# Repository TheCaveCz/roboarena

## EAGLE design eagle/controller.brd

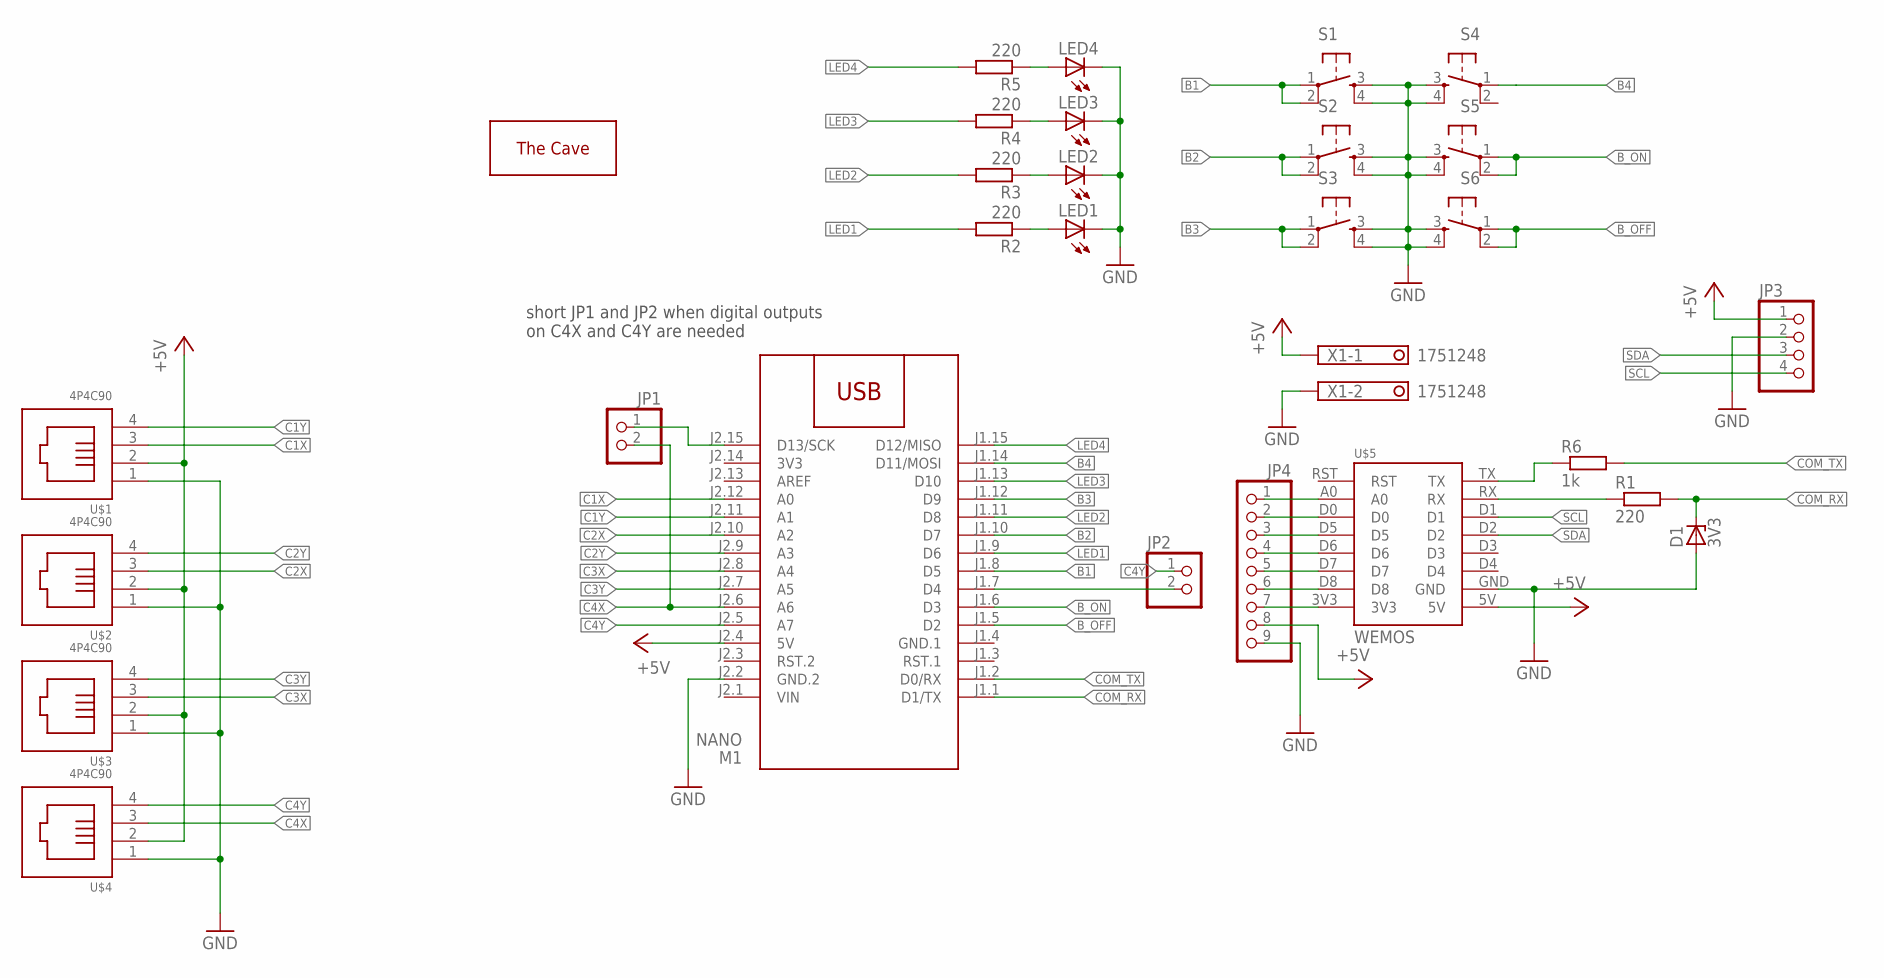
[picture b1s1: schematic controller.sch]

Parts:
D1: 3V3; ZDIO-7.5
JP1, JP2: PINHD-1X2; 1X02
JP3: PINHD-1X4; 1X04
JP4: PINHD-1X9; 1X09
LED1, LED2, LED3, LED4: LED5MM
M1: NANO; ARDUINO-NANO-3.0#NOHOLE
R1: 220; 0207/10
R2, R3, R4, R5: 220; R0805
R6: 1k; 0207/10
S1, S2, S3, S4, S5, S6: TACT-SWITCH-6MM-THT
U$1, U$2, U$3, U$4: 4P4C90; 4P4C-90
U$5: WEMOS
U$6: THECAVE_LOGO_NEW_TOP_SMALL; NEW_LOGO_SMALL_TOP
X1: 1751248

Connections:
3V3: M1.J2.14 (3V3)
+5V: JP3.1, JP4.8, M1.J2.4 (5V), U$1.2, U$2.2, U$3.2, U$4.2, U$5.5V, X1.1
B1: M1.J1.8 (D5), S1.1, S1.2
B2: M1.J1.10 (D7), S2.1, S2.2
B3: M1.J1.12 (D9), S3.1, S3.2
B4: M1.J1.14 (D11/MOSI), S4.1
B_OFF: M1.J1.5 (D2), S6.1, S6.2
B_ON: M1.J1.6 (D3), S5.1, S5.2
C1X: M1.J2.12 (A0), U$1.3
C1Y: M1.J2.11 (A1), U$1.4
C2X: M1.J2.10 (A2), U$2.3
C2Y: M1.J2.9 (A3), U$2.4
C3X: M1.J2.8 (A4), U$3.3
C3Y: M1.J2.7 (A5), U$3.4
C4X: JP1.2, M1.J2.6 (A6), U$4.3
C4Y: JP2.1, M1.J2.5 (A7), U$4.4
COM_RX: D1.C, M1.J1.1 (D1/TX), R1.2
COM_TX: M1.J1.2 (D0/RX), R6.2
GND: D1.A, JP3.2, JP4.9, LED1.K (C), LED2.K (C), LED3.K (C), LED4.K (C), M1.J2.2 (GND.2), S1.3, S1.4, S2.3, S2.4, S3.3, S3.4, S4.3, S4.4, S5.3, S5.4, S6.3, S6.4, U$1.1, U$2.1, U$3.1, U$4.1, U$5.GND, X1.2
GND.1: M1.J1.4 (GND.1)
LED1: M1.J1.9 (D6), R2.2
LED2: M1.J1.11 (D8), R3.2
LED3: M1.J1.13 (D10), R4.2
LED4: M1.J1.15 (D12/MISO), R5.2
unnamed: LED4.A, R5.1
unnamed: R1.1, U$5.RX
unnamed: LED3.A, R4.1
unnamed: LED2.A, R3.1
unnamed: LED1.A, R2.1
unnamed: JP1.1, M1.J2.15 (D13/SCK)
unnamed: JP2.2, M1.J1.7 (D4)
unnamed: JP4.2, U$5.D0
unnamed: JP4.3, U$5.D5
unnamed: JP4.4, U$5.D6
unnamed: JP4.5, U$5.D7
unnamed: JP4.6, U$5.D8
unnamed: JP4.1, U$5.A0
unnamed: R6.1, U$5.TX
unnamed: JP4.7, U$5.3V3
SCL: JP3.4, U$5.D1
SDA: JP3.3, U$5.D2
VIN: M1.J2.1 (VIN)

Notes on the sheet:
short JP1 and JP2 when digital outputs on C4X and C4Y are needed

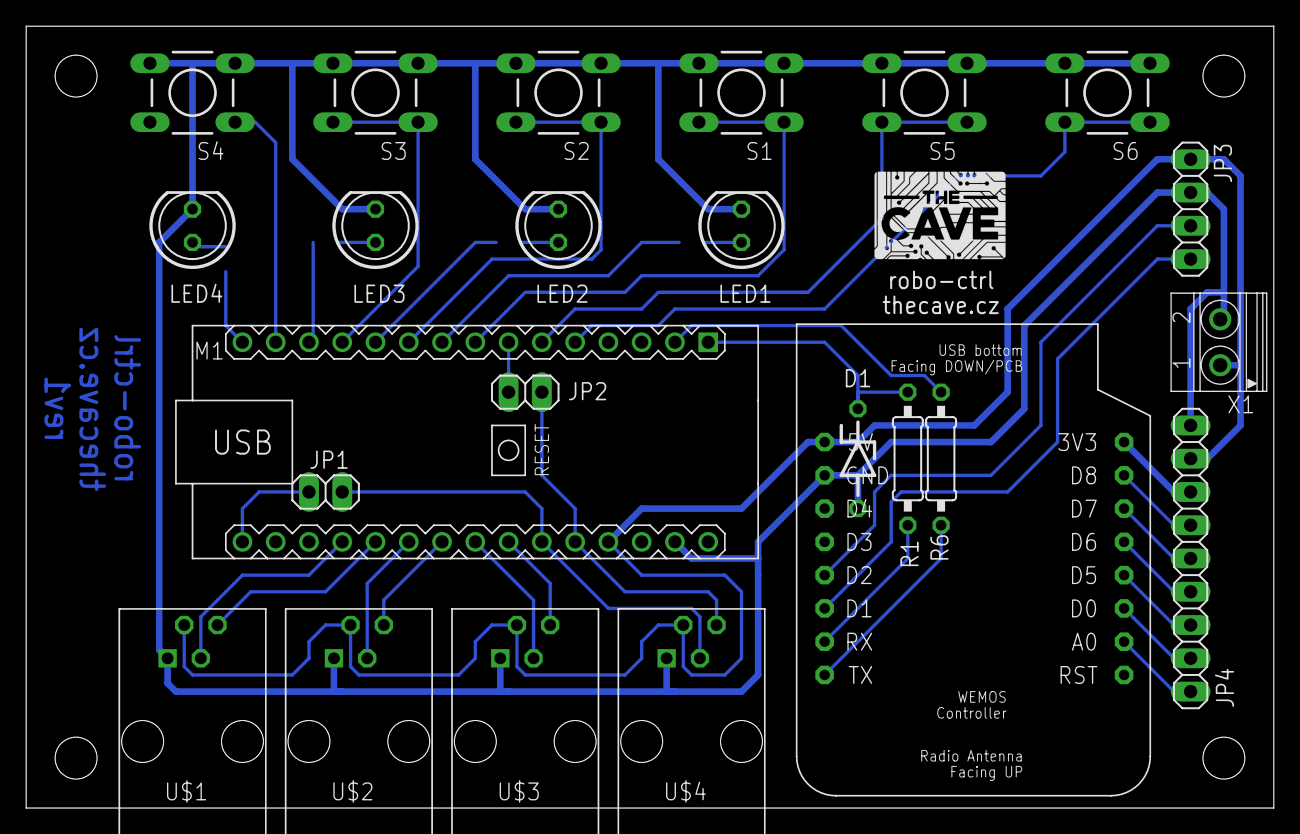
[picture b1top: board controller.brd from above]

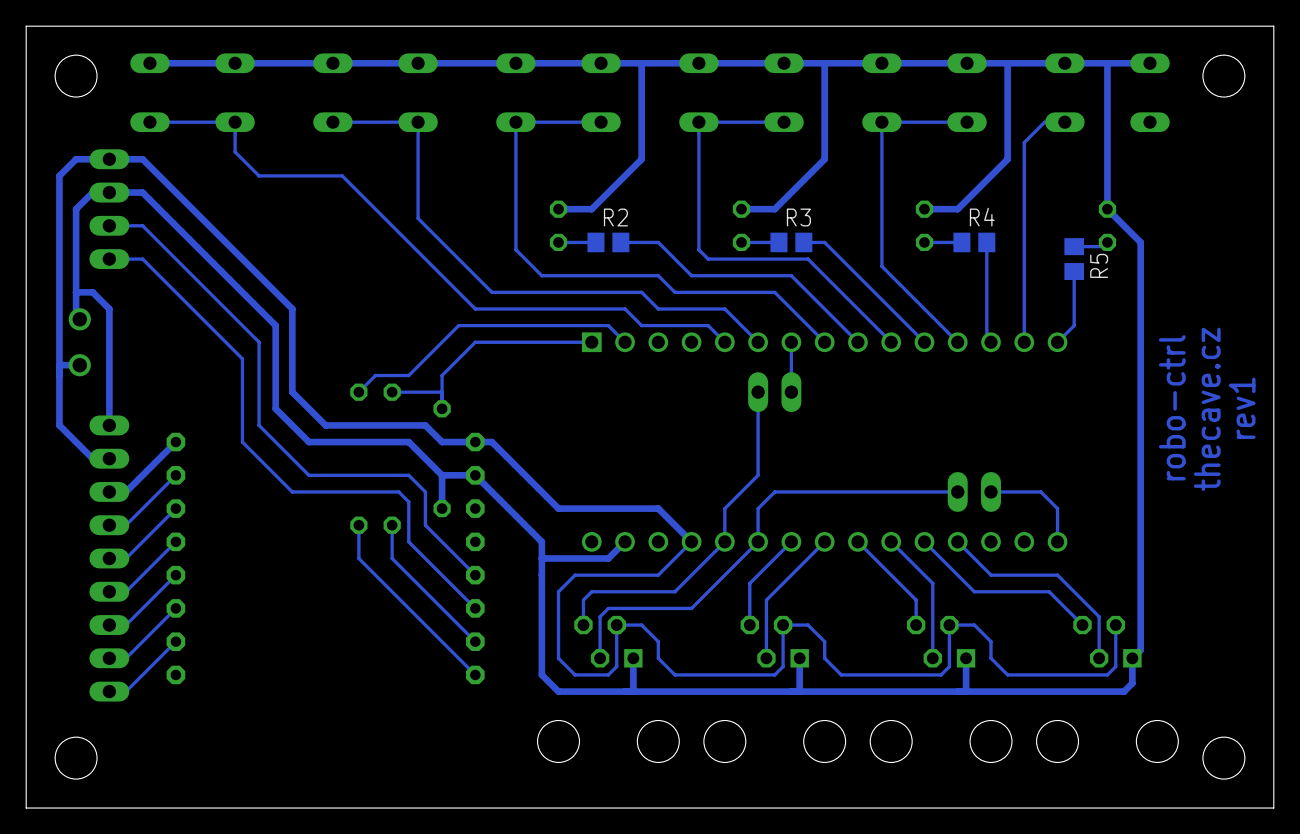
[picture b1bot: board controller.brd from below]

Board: 2 copper layers, 95.2 x 59.7 mm, 29 parts (4 on the bottom side), 39 nets.

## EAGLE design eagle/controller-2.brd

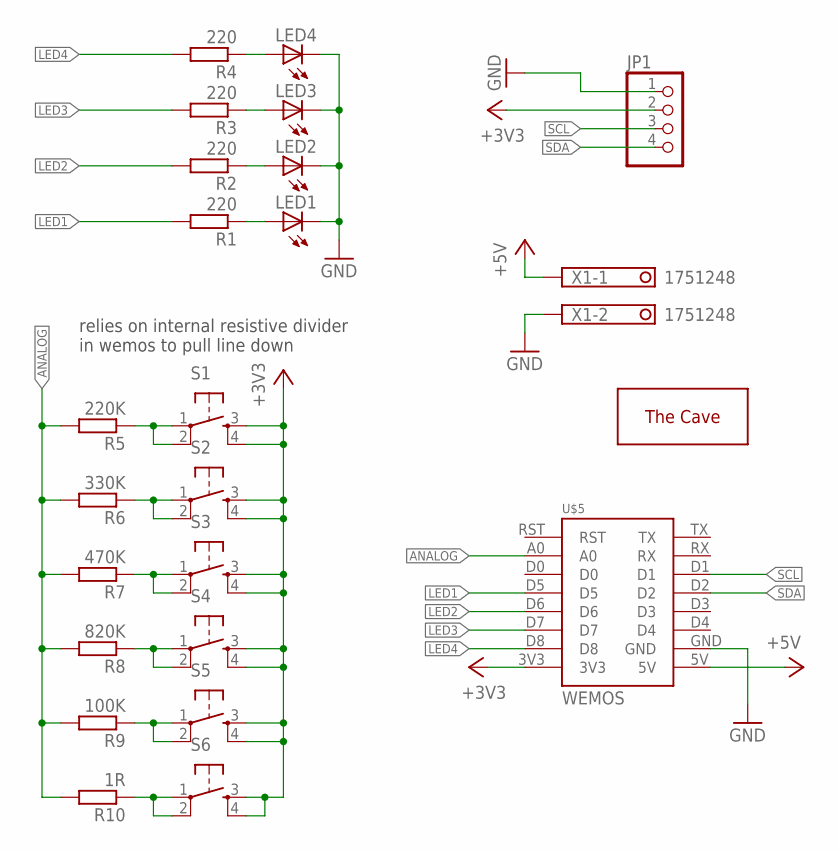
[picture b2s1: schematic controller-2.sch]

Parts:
JP1: PINHD-1X4; 1X04
LED1, LED2, LED3, LED4: LED5MM
R1, R2, R3, R4: 220; R0805
R5: 220K; R0805
R6: 330K; R0805
R7: 470K; R0805
R8: 820K; R0805
R9: 100K; R0805
R10: 1R; R0805
S1, S2, S3, S4, S5, S6: TACT-SWITCH-6MM-THT
U$1: THECAVE_LOGO_NEW_TOP_SMALL; NEW_LOGO_SMALL_TOP
U$5: WEMOS
X1: 1751248

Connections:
+3V3: JP1.2, S1.3, S1.4, S2.3, S2.4, S3.3, S3.4, S4.3, S4.4, S5.3, S5.4, S6.3, S6.4, U$5.3V3
+5V: U$5.5V, X1.1
ANALOG: R5.2, R6.2, R7.2, R8.2, R9.2, R10.2, U$5.A0
GND: JP1.1, LED1.K (C), LED2.K (C), LED3.K (C), LED4.K (C), U$5.GND, X1.2
LED1: R1.2, U$5.D5
LED2: R2.2, U$5.D6
LED3: R3.2, U$5.D7
LED4: R4.2, U$5.D8
unnamed: LED4.A, R4.1
unnamed: LED3.A, R3.1
unnamed: LED2.A, R2.1
unnamed: LED1.A, R1.1
unnamed: R10.1, S6.1, S6.2
unnamed: R9.1, S5.1, S5.2
unnamed: R8.1, S4.1, S4.2
unnamed: R7.1, S3.1, S3.2
unnamed: R6.1, S2.1, S2.2
unnamed: R5.1, S1.1, S1.2
SCL: JP1.3, U$5.D1
SDA: JP1.4, U$5.D2

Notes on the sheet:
relies on internal resistive divider in wemos to pull line down

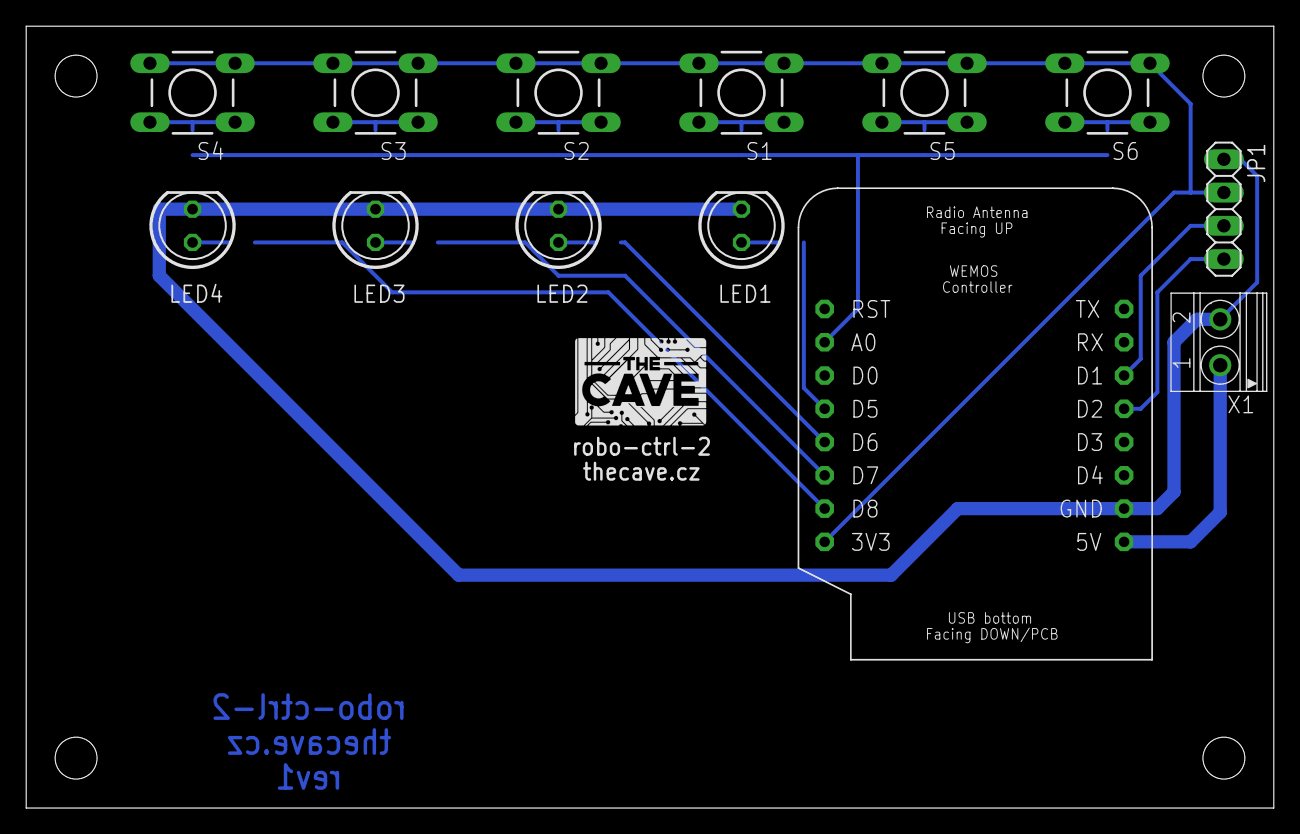
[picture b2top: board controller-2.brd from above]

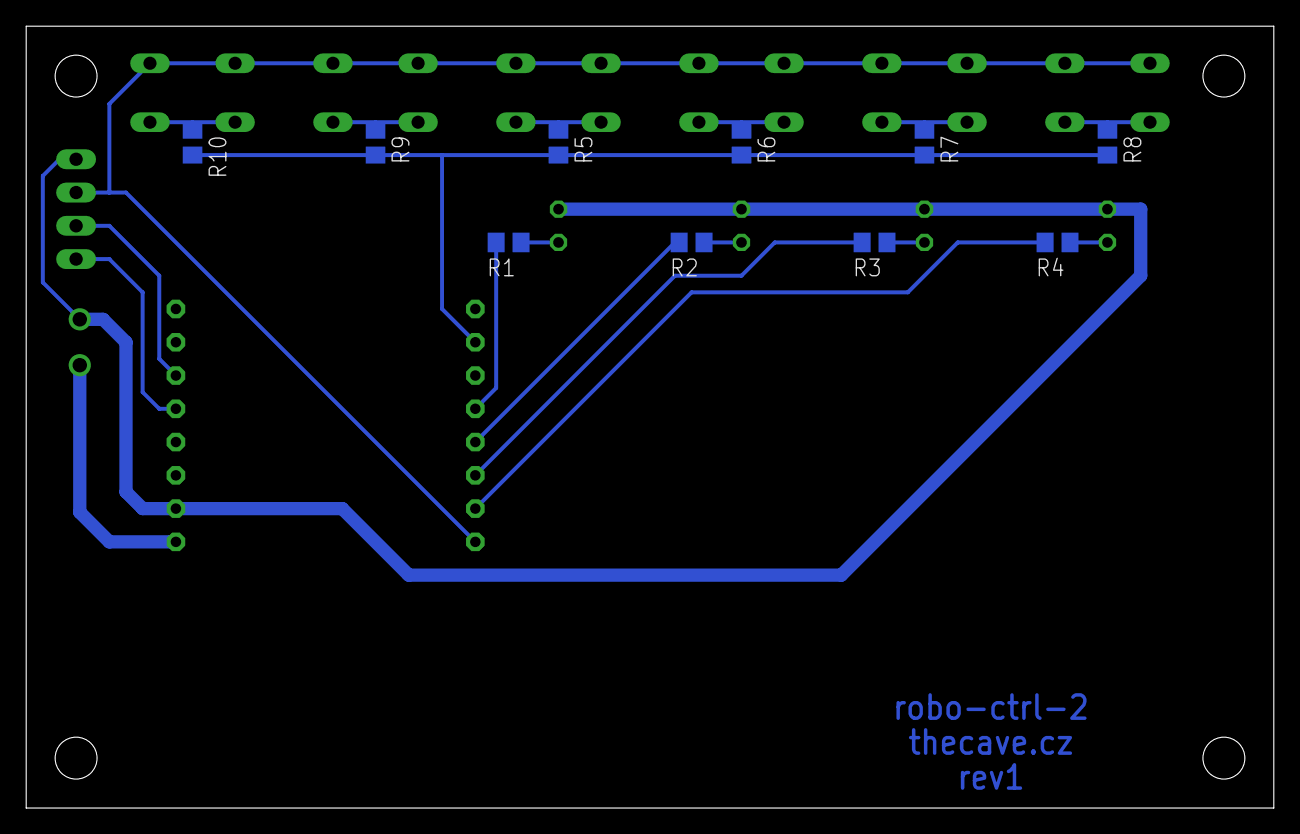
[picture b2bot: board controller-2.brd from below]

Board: 2 copper layers, 95.2 x 59.7 mm, 24 parts (10 on the bottom side), 20 nets.

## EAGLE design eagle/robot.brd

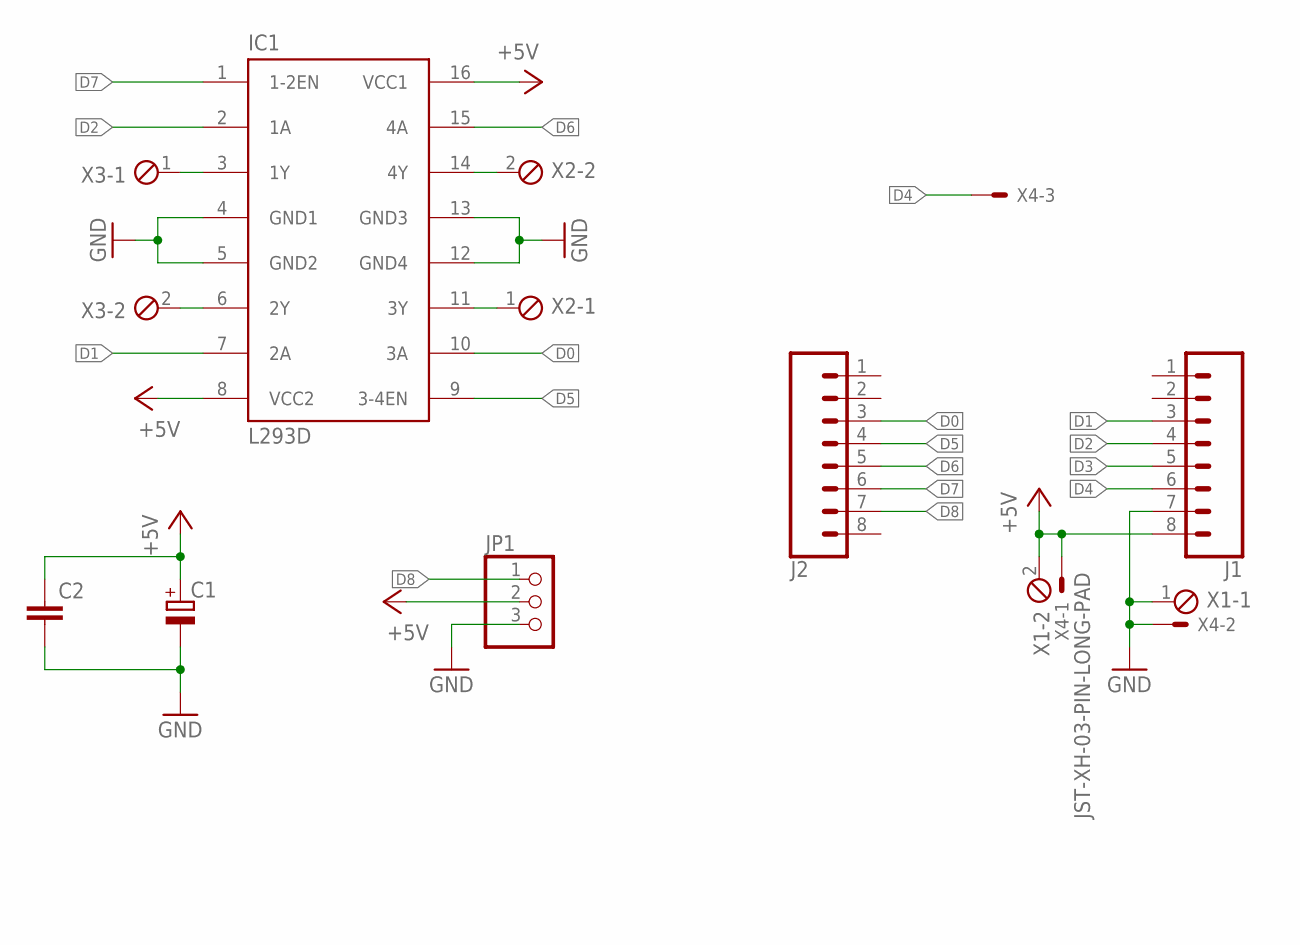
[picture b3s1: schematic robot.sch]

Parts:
C1: CPOL-EUE2.5-7; E2,5-7
C2: C-EUC0805K; C0805K
IC1: L293D; DIL16
J1, J2: CONN_08"; 1X08
JP1: PINHD-1X3; 1X03
X1, X2, X3: MPT2; 2POL254
X4: JST-XH-03-PIN-LONG-PAD; JST-XH-03-PACKAGE-LONG-PAD

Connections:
+5V: C1.+, C2.1, IC1.8 (VCC2), IC1.16 (VCC1), J1.8, JP1.2, X1.2, X4.1
D0: IC1.10 (3A), J2.3
D1: IC1.7 (2A), J1.3
D2: IC1.2 (1A), J1.4
D3: J1.5
D4: J1.6, X4.3
D5: IC1.9 (3-4EN), J2.4
D6: IC1.15 (4A), J2.5
D7: IC1.1 (1-2EN), J2.6
D8: J2.7, JP1.1
GND: C1.-, C2.2, IC1.4 (GND1), IC1.5 (GND2), IC1.12 (GND4), IC1.13 (GND3), J1.7, JP1.3, X1.1, X4.2
unnamed: IC1.3 (1Y), X3.1
unnamed: IC1.6 (2Y), X3.2
unnamed: IC1.11 (3Y), X2.1
unnamed: IC1.14 (4Y), X2.2

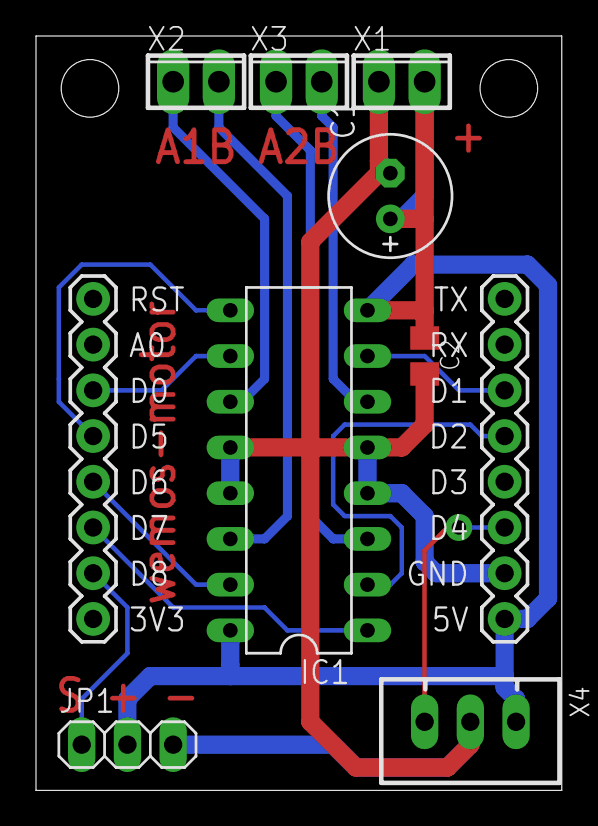
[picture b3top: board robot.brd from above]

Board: 2 copper layers, 29.2 x 41.9 mm, 10 parts (0 on the bottom side), 14 nets.

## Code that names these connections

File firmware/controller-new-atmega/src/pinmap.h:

#pragma once

#define PIN_BTN1 4
#define PIN_BTN2 3
#define PIN_BTN3 2
#define PIN_BTN4 9
#define PIN_BTN5 8
#define PIN_BTN6 7

#define PIN_LED1 6
#define PIN_LED2 5
#define PIN_LED3 10
#define PIN_LED4 13

#define PIN_C1X A4
#define PIN_C1Y A5
#define PIN_C2X A2
#define PIN_C2Y A3
#define PIN_C3X A0
#define PIN_C3Y A1
#define PIN_C4X A6
#define PIN_C4Y A7

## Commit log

2019-02-28 PCB tweaks
2019-02-28 Add firmware for controller 2
2019-03-08 Add app and photo
2019-09-19 Add coil holder models
2019-09-19 [FW-robot] Improve OTA logging
2019-09-19 [FW] Add new command opcodes
2019-09-19 [FW-robot] Add life counting logic and brighter LEDs
2019-09-19 [FW-robot] Add rfid reader code
2019-09-19 [FW-robot] New hit and set life commands
2019-09-20 [FW-controller2] Button long press support
2019-09-20 [FW-robot] Update for 6 neopixels
2019-09-20 [FW-robot] Parse readers with binary crc
2019-09-20 [FW-robot] Adjust brake anim with 0 life
2019-09-20 [FW-robot] Remove chip debounce logic
2019-09-20 [FW-robot] Adjust pwm min max values and pwm freq
2019-09-20 [FW-robot] RoboId in hostname
2019-09-20 [FW-controller-wemos] Add deadzones for joystick axes
2019-09-20 [FW-robot] Tune minimum pwm
2019-09-21 [FW-robot] Use D3 and software serial for RFID reader
2019-09-21 [FW-robot] remove debug
2020-02-29 [stl] Add box for new version of control board
2020-02-29 [stl] Add more space around connectors
2020-03-02 [FW] New controller firmware
2020-03-02 [stl] Add new robot frame and update control box dimensions
2020-03-03 [fw] update controller firmware
2020-03-04 [fw] finished basic version of controller fw
2020-03-04 [stl] remote controller case
2020-03-05 [fw] robot-esp32 basic project and mp3 decoder
2020-03-12 [FW] robot-esp32 firmware
2020-03-13 [fw-robot] vbat calibration, add OTA, fix anim bug
2020-03-13 [fw-control] add robot presence detect
2020-03-13 [stl] add models
2020-03-13 [fw-robot] finishing touches
2022-02-11 [stl] Adjust robot frame model
2022-02-11 [misc] Add wifi password to gitignore
2022-06-23 [fw] Use symlinks instead of shared dir for libraries
2022-06-23 [fw-control] Use esp-now instead of wifi udp broadcast
2022-06-23 [fw-control] Reduce atmega-esp baudrate, improve command handling
2022-06-23 [fw-control] Improve presence indication
2022-06-24 [fw-robot] Use esp-now instead of wifi udp
2022-06-24 [fw] Improve controller response by adding mapping curves
2022-06-24 [fw-robot] Indicate boost mode
2022-06-26 [fw-robot] play boost sound
2022-06-26 [fw] Add signal firmware
2022-07-02 [stl] Improved baloon mount

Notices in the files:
parts and their libraries:
diy-modules: Released under the Creative Commons Attribution 4.0 International License: http://creativecommons.org/licenses/by/4.0
SparkFun-Connectors: Licensing: Creative Commons ShareAlike 4.0 International - https://creativecommons.org/licenses/by-sa/4.0
